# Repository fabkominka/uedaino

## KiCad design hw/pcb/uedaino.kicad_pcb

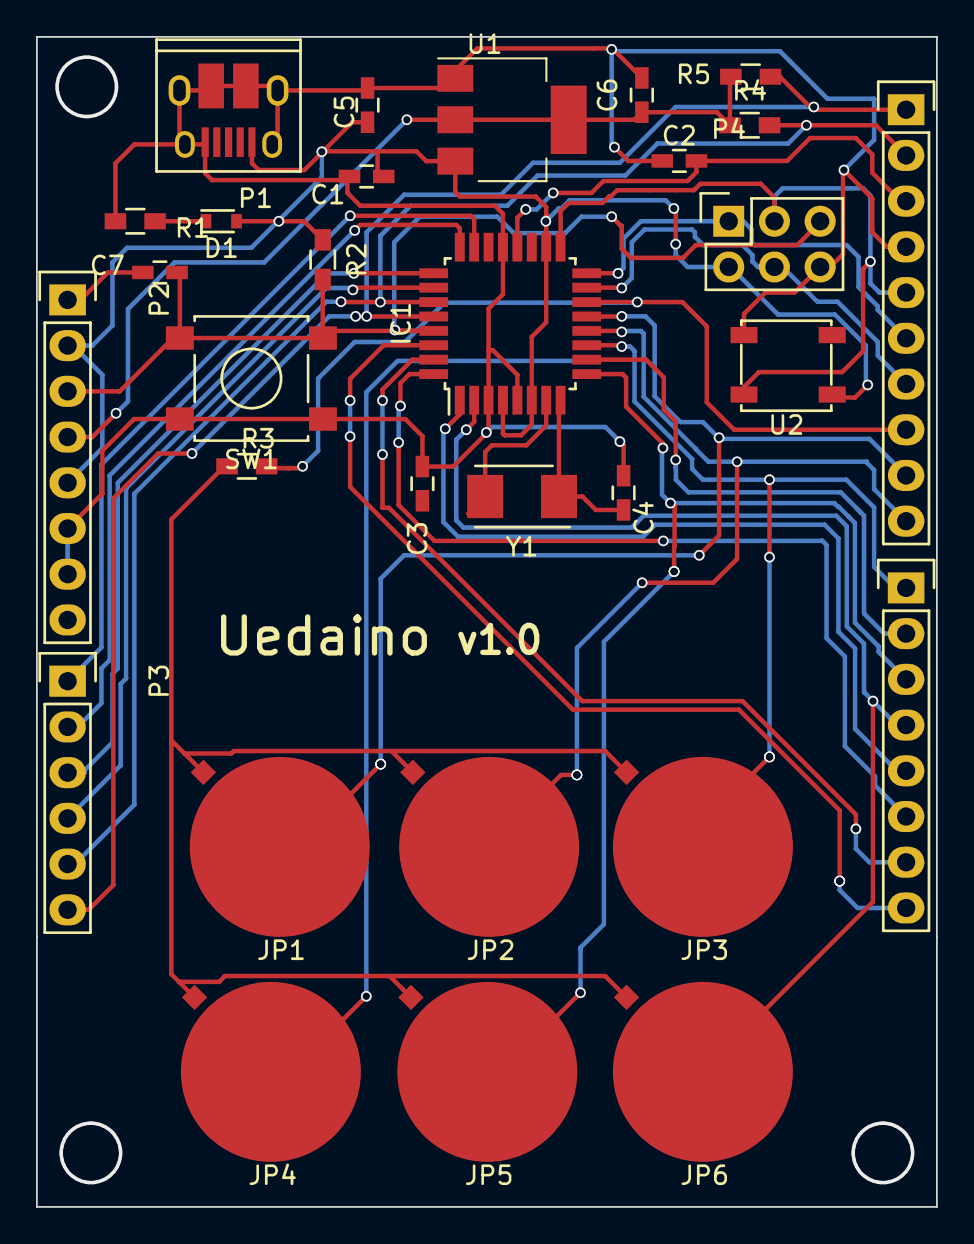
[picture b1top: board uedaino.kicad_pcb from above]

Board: 2 copper layers, 50.0 x 65.0 mm, 30 parts (0 on the bottom side), 30 nets.

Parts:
C1, C2, C7: 0.1u; C_0603_HandSoldering
C3, C4: 22uF; C_0603_HandSoldering
C5, C6: 10uF; C_0603_HandSoldering
D1: LED_+5V; D_0603
IC1: ATMEGA328P-A; TQFP-32_7x7mm_Pitch0.8mm
JP1: J_CAP1; JP_CAP
JP2: J_CAP2; JP_CAP
JP3: J_CAP3; JP_CAP
JP4: J_CAP4; JP_CAP
JP5: J_CAP5; JP_CAP
JP6: J_CAP6; JP_CAP
P1: USB_OTG; USB_Micro-B_10103594-0001LF
P2: CN_POWER; Socket_Strip_Straight_1x08
P3: CN_J1; Socket_Strip_Straight_1x06
P4: CN_ICSP; Socket_Strip_Straight_2x03
P5: CONN_01X10; Socket_Strip_Straight_1x10
P6: CONN_01X08; Socket_Strip_Straight_1x08
R1: 1K; R_0603_HandSoldering
R2: 10K; R_0603_HandSoldering
R3: 10M; R_0603_HandSoldering
R4, R5: 3.3K; R_0603_HandSoldering
SW1: SW_PUSH; SW_SPST_B3S-1000
U1: AP1117; SOT-223
U2: WS2812B
Y1: 16MHz; Crystal_SMD_5032_2Pads

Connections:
+3V3: C6.1, P2.4, R4.1, R5.1, U1.2, U1.4
+5V: C1.1, C5.1, D1.2, IC1.4, IC1.6, IC1.18, P1.1, P2.2, P2.5, P4.2, R2.1, U1.3, U2.1
/A0: IC1.23, P3.1
/A1: IC1.24, P3.2
/A2: IC1.25, P3.3
/A3: IC1.26, P3.4
/A4/SDA: IC1.27, P3.5, P5.2, R4.2
/A5/SCL: IC1.28, P3.6, P5.1, R5.2
/AREF: C2.1, IC1.20, P5.3
/D2: IC1.32, P6.6
/D3: IC1.1, P6.5
/D4: IC1.2, JP6.1, P6.4
/D5: IC1.9, JP5.1, P6.3
/D6: IC1.10, JP4.1, P6.2
/D7: IC1.11, JP3.1, P6.1
/D8: IC1.12, JP2.1, P5.10
/D9: IC1.13, JP1.1, P5.9
/D10: IC1.14, P5.8, R3.1
/D11/MOSI: IC1.15, P4.4, P5.7
/D12/MISO: IC1.16, P4.1, P5.6
/D13/SCK: IC1.17, P4.3, P5.5, U2.4
/DTR: C7.1, P2.1
/RESET: C7.2, IC1.29, P2.3, P4.5, R2.2, SW1.2
/RXD: IC1.30, P6.8
/TXD: IC1.31, P6.7
/XT1: C3.1, IC1.7, Y1.2
/XT2: C4.2, IC1.8, Y1.1
GND: C1.2, C2.2, C3.2, C4.1, C5.2, C6.2, IC1.3, IC1.5, IC1.21, P1.5, P1.6, P2.6, P2.7, P4.6, P5.4, R1.2, SW1.1, U1.1, U2.3
unnamed: D1.1, R1.1
unnamed: JP1.2, JP2.2, JP3.2, JP4.2, JP5.2, JP6.2, R3.2

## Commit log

2016-11-08 Add reveal.js files.
2016-11-08 Rename reveal.js's LICENSE and README.
2016-11-08 Add contents.
2016-11-08 Disable title uppercase.
2016-11-08 Fix title.
2016-12-11 Move the presentation file under docs.
2016-12-11 Add the kicad files.
2016-12-23 Add functions
    Add power circuit.
    Add Capacitive Touch Sensor circuit.
    Add pin header.
2017-01-08 Import kobayutapon's update
2017-01-08 Support Arduino Pinout
2017-01-08 Remove XTAL
2017-01-08 Remove ICSP
2017-01-08 Remove I2C
2017-01-08 Roughly placed the components
2017-01-09 Add PCB Design
2017-01-11 Add lib
2017-01-12 Fix error
2017-01-12 Fix layout
2017-01-12 Add silk
2017-01-12 Add ground fill
2017-01-12 Export gerber files
2017-02-01 Add bom
2017-02-01 Fix BOM
